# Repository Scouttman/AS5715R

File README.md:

# AS5715R
Inductive encoder based off the as5715r from AMS

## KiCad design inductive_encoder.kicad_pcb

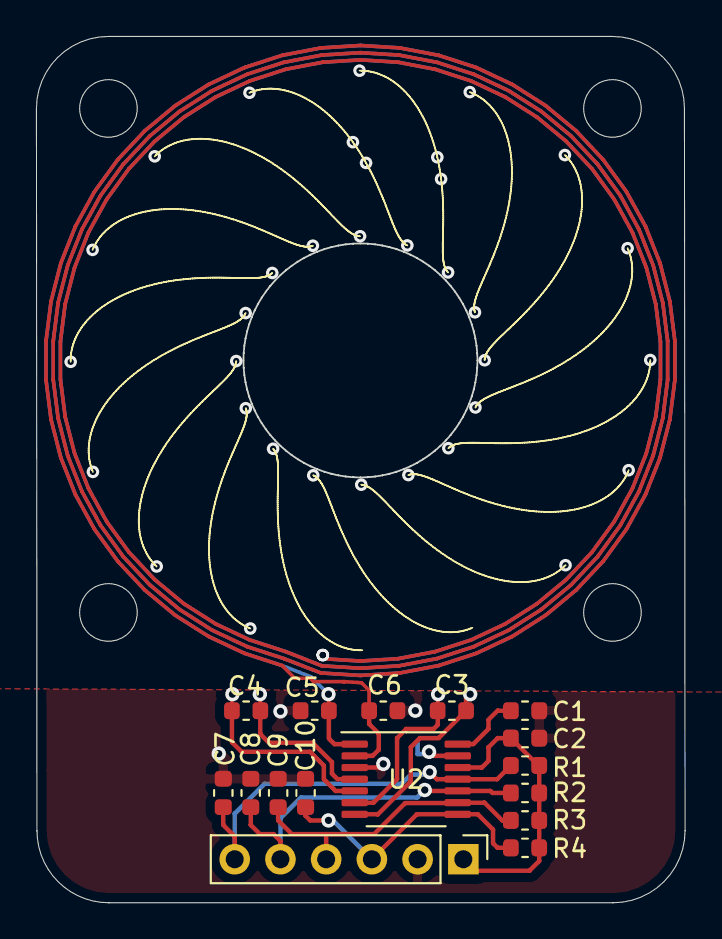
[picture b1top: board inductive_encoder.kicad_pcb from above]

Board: 4 copper layers, 36.0 x 48.1 mm, 20 parts (0 on the bottom side), 10 nets.

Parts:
C1: 200nF; C_0603_1608Metric
C2: 100nF; C_0603_1608Metric
C3, C4: tbd; C_0603_1608Metric
C5, C6: 1.2n; C_0603_1608Metric
C7, C8, C9, C10: 47n; C_0603_1608Metric
H1, H2, H3, H4: MountingHole_Pad; MountingHole_3.2mm_M3
J1: Conn_01x06_Male; PinHeader_1x06_P2.54mm_Vertical
R1, R2, R3, R4: 6.8k; R_0603_1608Metric
U2: AS5715R; TSSOP-14_4.4x5mm_P0.65mm

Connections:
COS+_SCL: C9.1, J1.4, R3.2, U2.9
COS-: C10.1, J1.3, R4.2, U2.8
GND: C1.1, C2.1, C5.1, C6.1, C7.2, C8.2, C9.2, C10.2, J1.2, U2.3, U2.13
unnamed: C1.2, U2.14
RXCA: C4.1, C4.2, U2.4, U2.5
RXCB: C3.1, C3.2, U2.6, U2.7
SIN+_SDA: C7.1, J1.6, R1.2, U2.11
SIN-: C8.1, J1.5, R2.2, U2.10
TXB: C5.2, C6.2, U2.1, U2.2
VCC: C2.2, J1.1, R1.1, R2.1, R3.1, R4.1, U2.12

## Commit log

2021-12-12 script to generate indutive encoder coils and the schematic to go with it
2021-12-12 screen shot
2025-06-01 Created using Colab
